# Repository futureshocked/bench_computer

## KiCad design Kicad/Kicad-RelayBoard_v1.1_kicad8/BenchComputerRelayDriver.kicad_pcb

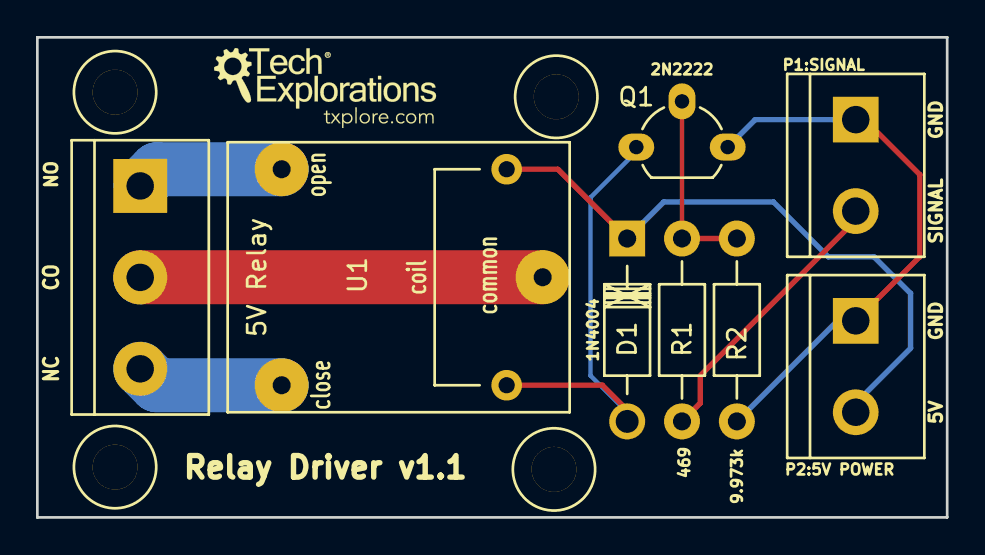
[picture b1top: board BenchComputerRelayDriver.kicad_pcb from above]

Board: 2 copper layers, 50.5 x 26.7 mm, 8 parts (0 on the bottom side), 8 nets.

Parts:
D1: D; Diode_DO-41_SOD81_Horizontal_RM10
P1:SIGNAL, P2:5V POWER: CONN_01X02; bornier2
P3: CONN_01X03; bornier3
Q1: 2N2222; TO-92_Molded_Wide_Oval
R1, R2: R; Resistor_Horizontal_RM10mm
U1: 5V/10A_relay; SONGLE_5V_Relay

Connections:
/signal_in: P1:SIGNAL.2, R1.2
GND: P1:SIGNAL.1, P2:5V POWER.1, Q1.3, R2.2
unnamed: D1.1, P2:5V POWER.2, U1.1
unnamed: D1.2, Q1.2, U1.2
unnamed: P3.1, U1.4
unnamed: P3.2, U1.3
unnamed: P3.3, U1.5
unnamed: Q1.1, R1.1, R2.1

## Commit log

2016-06-03 First commit.
2016-06-03 Added info header. Fixed a bug that caused the DHT22 sensor to hung after a few read cycles.
2016-06-03 Added code to confirm closing the program, and to tidy up before closing.
2016-06-04 Added licensed icons.
2016-07-14 Added icon files about.
2016-07-22 Added Kicad project files.
2016-07-23 A template suplicant file for your Wifi network
2016-07-25 Added example session for the PFR X Port.
2016-07-27 Added tkinter example code.
2016-07-27 Added some header informattion.
2016-07-27 Added final app script versions.
2016-07-27 Moved the icons About file.
2016-08-01 Added split recording example script.
2016-08-03 Added dht22 demo that works with the pigpio deamon.
2016-08-15 Added the updated version of the relay PCB Kicad project and Gerber files.
2016-08-15 Removed.
2018-01-11 cleaning up.
2018-01-18 New version covers generic relay boards like the Keyestudio 4 channel relay HAT.
2018-01-25 Added sample scripts for the Keyestudio relay board.
2018-01-29 Added Keith Hoard's CAD file for the deluxe enclosure.
2018-04-02 Added "self" to cameraFrameLeft.
2019-10-07 removed extra parenthesis on line 93
2022-08-04 Upgraded project for KiCad 6
2023-06-29 Improve file names
    As per yn1v's recommendation, this change creates file names that are in the correct order.
2024-10-18 Contributed code for Picamera2
    Since Bullseye no longer supports Picamera, we need to use Picamera2 to access the RPi camera functionality.
    I put together a few script files that do some of the same things that were discussed in the lectures while using Picamaera.
    I also included a pdf file that outlines some of the Picamera2 functionality plus outlines what is in the script files which I included. Some of the script files might have more than you need but the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
    Author: Howard Chernick
    eMail: hchernick@comcast.net
2024-10-20 Update Py3_example_Hello_World_v4.py
    Addressing an issue with the var_changed event, where the a_var variable gets garbage collected and lost.
